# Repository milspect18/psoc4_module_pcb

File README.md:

# PSOC4 Module PCB
A very small footprint PSOC 4000 module for microcontroller projects.

The PSOC4 CY8C4246PVI-DS402 microcontroller includes an integrated low-dropout power regulator which means it can be wired directly to a small 3.7 v lipo battery.  This module includes the necessary de-coupling capacitors to filter input power, as well as a pull-up resistor for the reset line.  The only other thing on the board is a 10-pin 1.27mm 2x5 ARM SWD debug header for firmware loading and debugging.

This project has been uploaded to OSH Park and can be ordered here: https://oshpark.com/shared_projects/bZPw8Fch

The board has been made and tested to work.

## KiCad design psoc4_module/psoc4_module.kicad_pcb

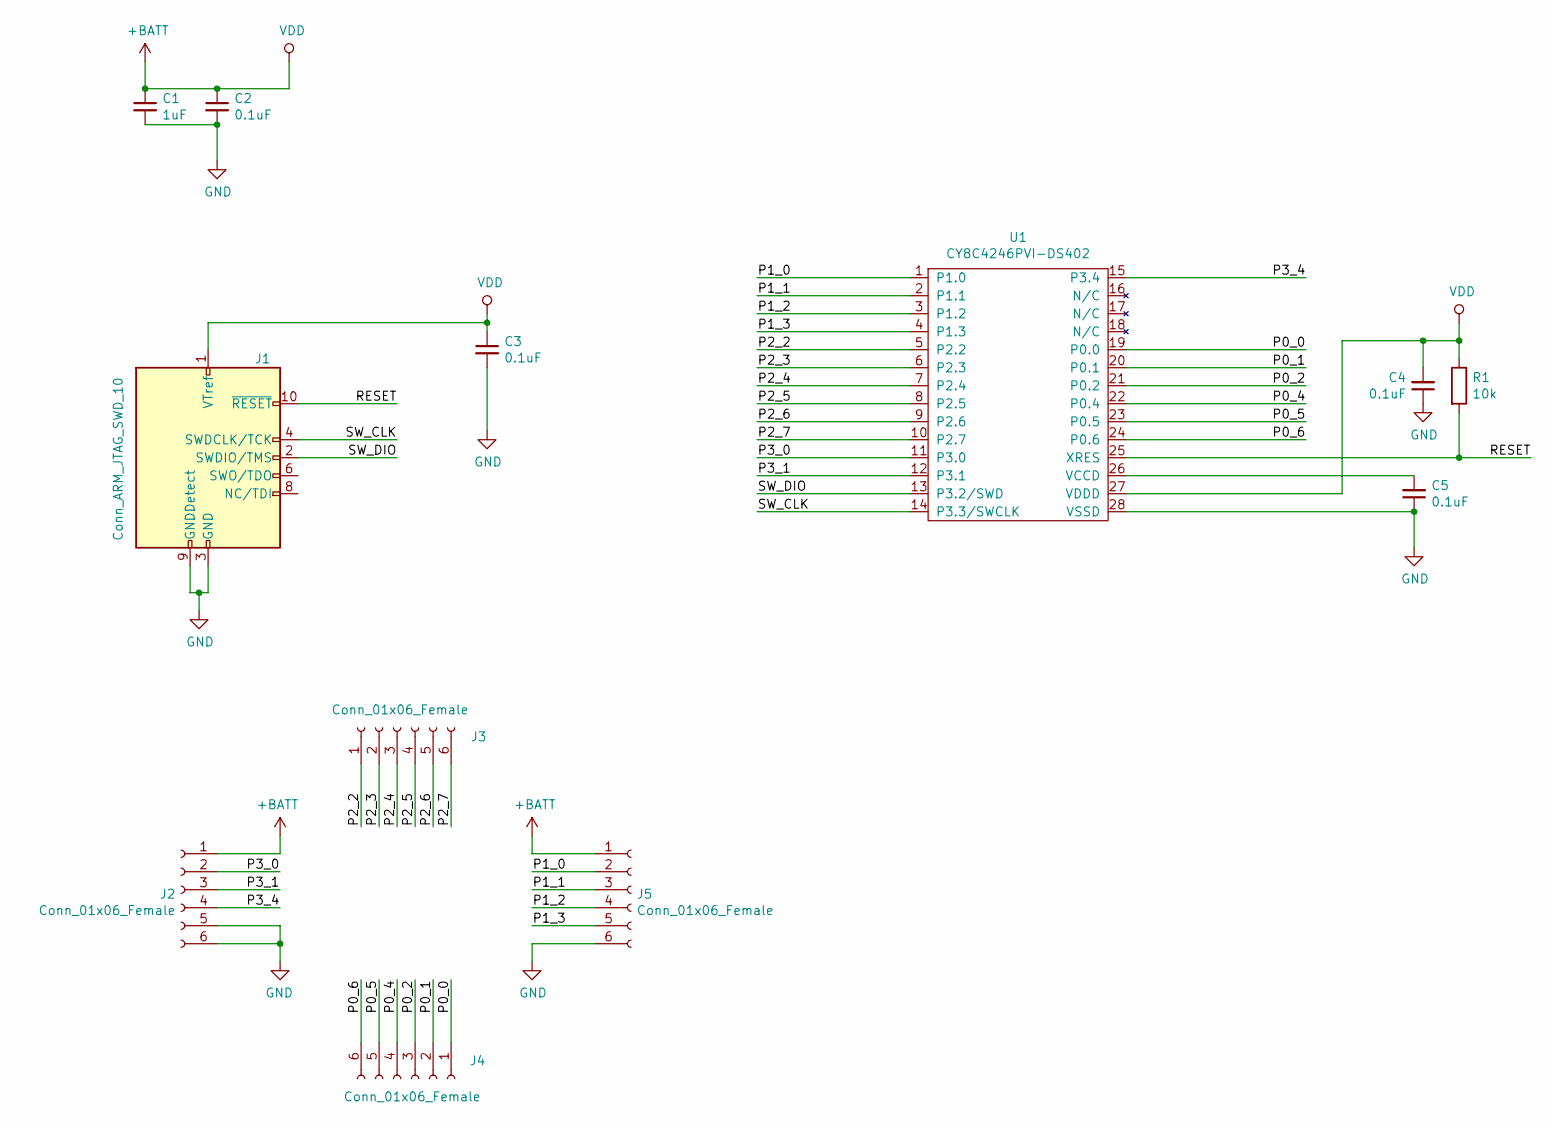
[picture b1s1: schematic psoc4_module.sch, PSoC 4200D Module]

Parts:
C1: 1uF; C_0603_1608Metric_Pad1.05x0.95mm_HandSolder
C2, C3, C4, C5: 0.1uF; C_0603_1608Metric_Pad1.05x0.95mm_HandSolder
J1: Conn_ARM_JTAG_SWD_10; PinHeader_2x05_P1.27mm_Vertical_SMD
J2, J3, J4, J5: Conn_01x06_Female; 01x06_Casellated
R1: 10k; R_0603_1608Metric_Pad1.05x0.95mm_HandSolder
U1: CY8C4246PVI-DS402; SSOP-28_5.3x10.2mm_P0.65mm

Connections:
+BATT: C1.1, C2.1, C3.1, C4.2, J1.1 (VTref), J2.1, J5.1, R1.1, U1.27 (VDDD)
/P0_0: J4.1, U1.19 (P0.0)
/P0_1: J4.2, U1.20 (P0.1)
/P0_2: J4.3, U1.21 (P0.2)
/P0_4: J4.4, U1.22 (P0.4)
/P0_5: J4.5, U1.23 (P0.5)
/P0_6: J4.6, U1.24 (P0.6)
/P1_0: J5.2, U1.1 (P1.0)
/P1_1: J5.3, U1.2 (P1.1)
/P1_2: J5.4, U1.3 (P1.2)
/P1_3: J5.5, U1.4 (P1.3)
/P2_2: J3.1, U1.5 (P2.2)
/P2_3: J3.2, U1.6 (P2.3)
/P2_4: J3.3, U1.7 (P2.4)
/P2_5: J3.4, U1.8 (P2.5)
/P2_6: J3.5, U1.9 (P2.6)
/P2_7: J3.6, U1.10 (P2.7)
/P3_0: J2.2, U1.11 (P3.0)
/P3_1: J2.3, U1.12 (P3.1)
/P3_4: J2.4, U1.15 (P3.4)
/RESET: J1.10 (~RESET~), R1.2, U1.25 (XRES)
/SW_CLK: J1.4 (SWDCLK/TCK), U1.14 (P3.3/SWCLK)
/SW_DIO: J1.2 (SWDIO/TMS), U1.13 (P3.2/SWD)
GND: C1.2, C2.2, C3.2, C4.1, C5.1, J1.3 (GND), J1.5 (GND), J1.9 (GNDDetect), J2.5, J2.6, J5.6, U1.28 (VSSD)
unnamed: C5.2, U1.26 (VCCD)

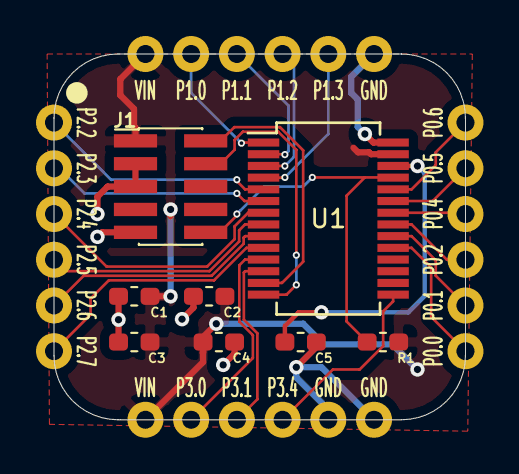
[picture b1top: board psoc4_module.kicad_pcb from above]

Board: 2 copper layers, 22.9 x 20.3 mm, 12 parts (0 on the bottom side), 25 nets.

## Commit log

2020-05-20 Add KiCad project and supporting lib components
2020-05-20 Initial KiCad project and custom lib components
2020-05-20 Remove superflous artifacts from botched upload
